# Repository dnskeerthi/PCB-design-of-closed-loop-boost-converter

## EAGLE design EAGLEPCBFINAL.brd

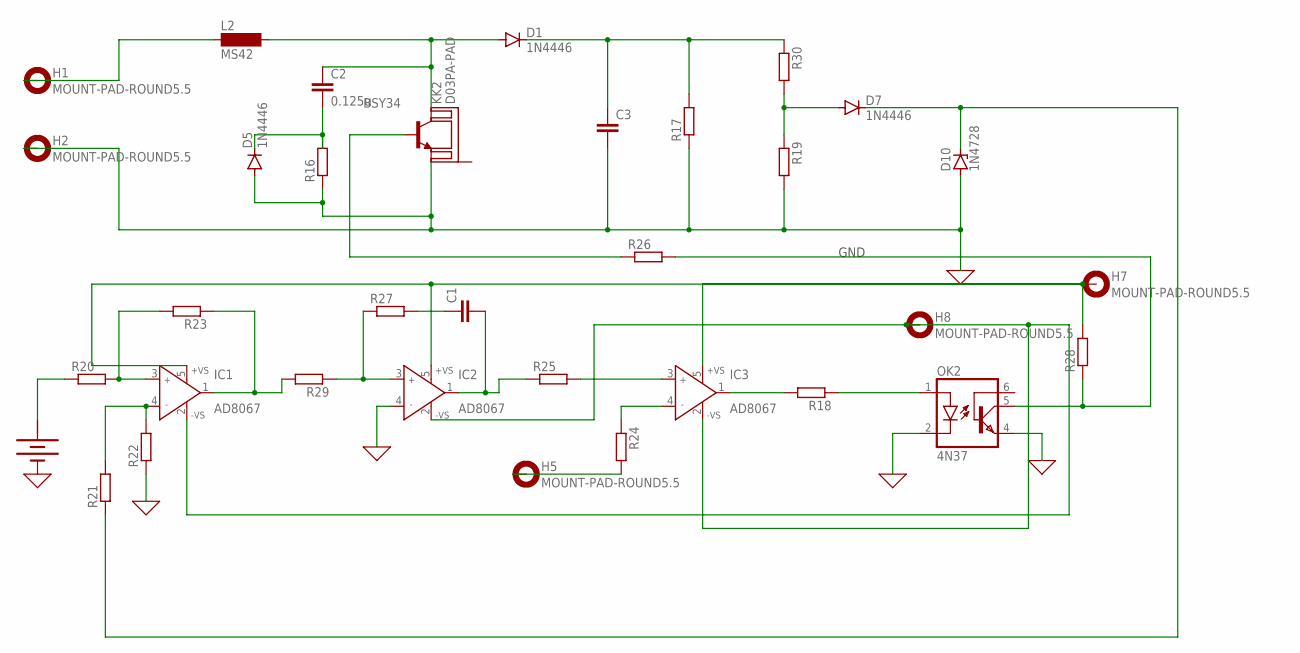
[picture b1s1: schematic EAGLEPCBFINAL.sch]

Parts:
BAT1: BATTERY
C1: C2.5/2; C2.5-2
C2: 0.125u; C5B3.5
C3: C7.5/3; C7.5B3
D1, D5, D7: 1N4446; DO35-10
D10: 1N4728; DO41Z10
H1, H2, H5, H7, H8: MOUNT-PAD-ROUND5.5; 5,5-PAD
IC1, IC2, IC3: AD8067; SOT23-5
KK2: D03PA-PAD
L2: MS42
OK2: 4N37; DIL06
R16, R17: R-EU_0204/2V; 0204V
R18: R-EU_0204/5; 0204/5
R19, R20, R21, R22, R23, R24, R25, R26: R-EU_0207/10; 0207/10
R27: R-EU_0309/12; 0309/12
R28, R29: R-EU_0411/15; 0411/15
R30: R-EU_0922/22; 0922/22
T1: BSY34; TO39

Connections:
0: BAT1.-, C3.2, D5.A, D10.A, H2.B5,5, IC2.4 (IN-), OK2.2 (C), OK2.4 (EMI), R16.1, R17.1, R19.2, R22.1, T1.1 (E)
+: BAT1.+@1 (+)
unnamed: H1.B5,5, L2.1
unnamed: C2.1, D1.A, L2.2, T1.3 (C)
unnamed: C3.1, D1.C, R17.2, R30.1
unnamed: D7.A, R19.1, R30.2
unnamed: C2.2, D5.C, R16.2
unnamed: H8.B5,5, IC1.2 (-VS), IC2.2 (-VS), IC3.2 (-VS)
unnamed: D7.C, D10.C, R21.1
unnamed: BAT1.+, R20.1
unnamed: IC1.3 (IN+), R20.2, R23.2
unnamed: IC1.4 (IN-), R21.2, R22.2
unnamed: IC1.1 (OUT), R23.1, R29.2
unnamed: IC2.3 (IN+), R27.1, R29.1
unnamed: C1.1, R27.2
unnamed: C1.2, IC2.1 (OUT), R25.1
unnamed: IC3.3 (IN+), R25.2
unnamed: IC3.4 (IN-), R24.1
unnamed: IC3.1 (OUT), R18.2
unnamed: OK2.1 (A), R18.1
unnamed: OK2.5 (COL), R26.2, R28.1
unnamed: H7.B5,5, IC1.5 (+VS), IC2.5 (+VS), IC3.5 (+VS), R28.2
unnamed: R26.1, T1.2 (B)
unnamed: H5.B5,5, R24.2

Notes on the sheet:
GND

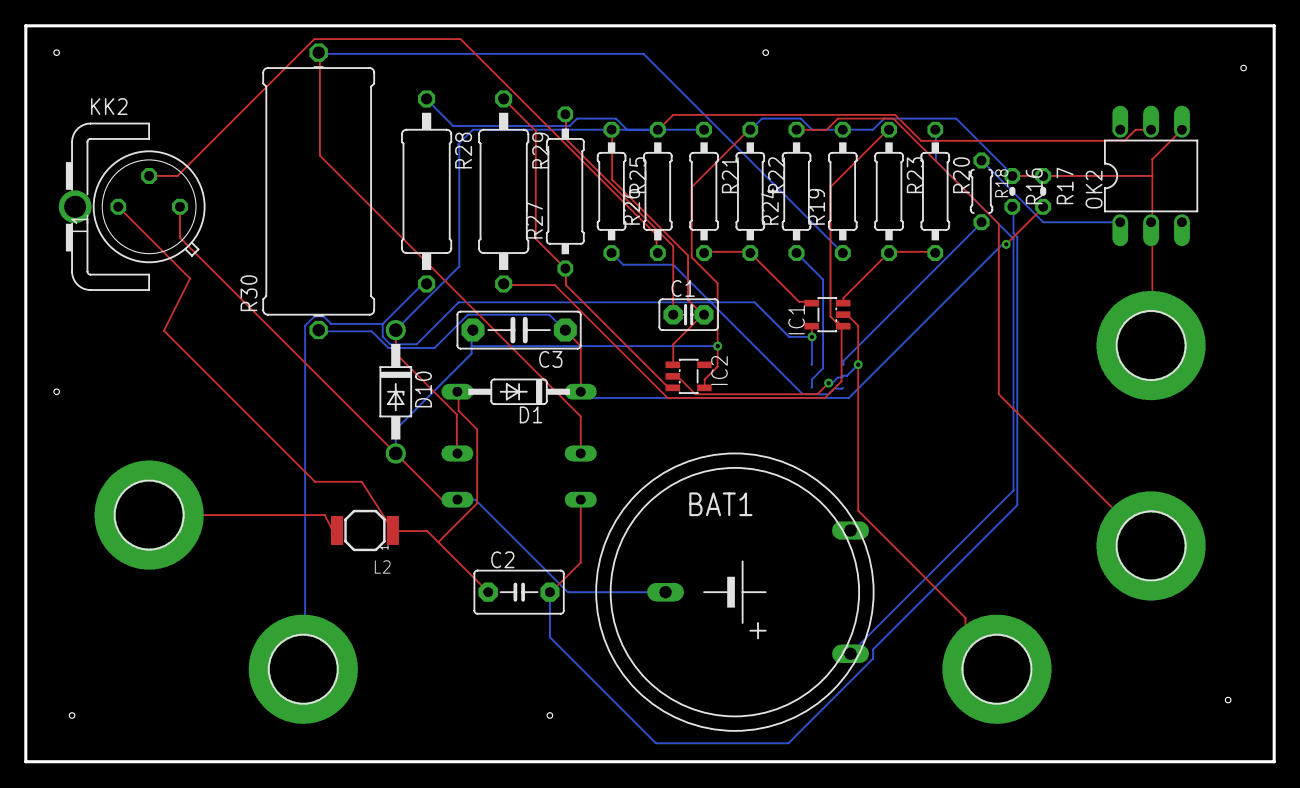
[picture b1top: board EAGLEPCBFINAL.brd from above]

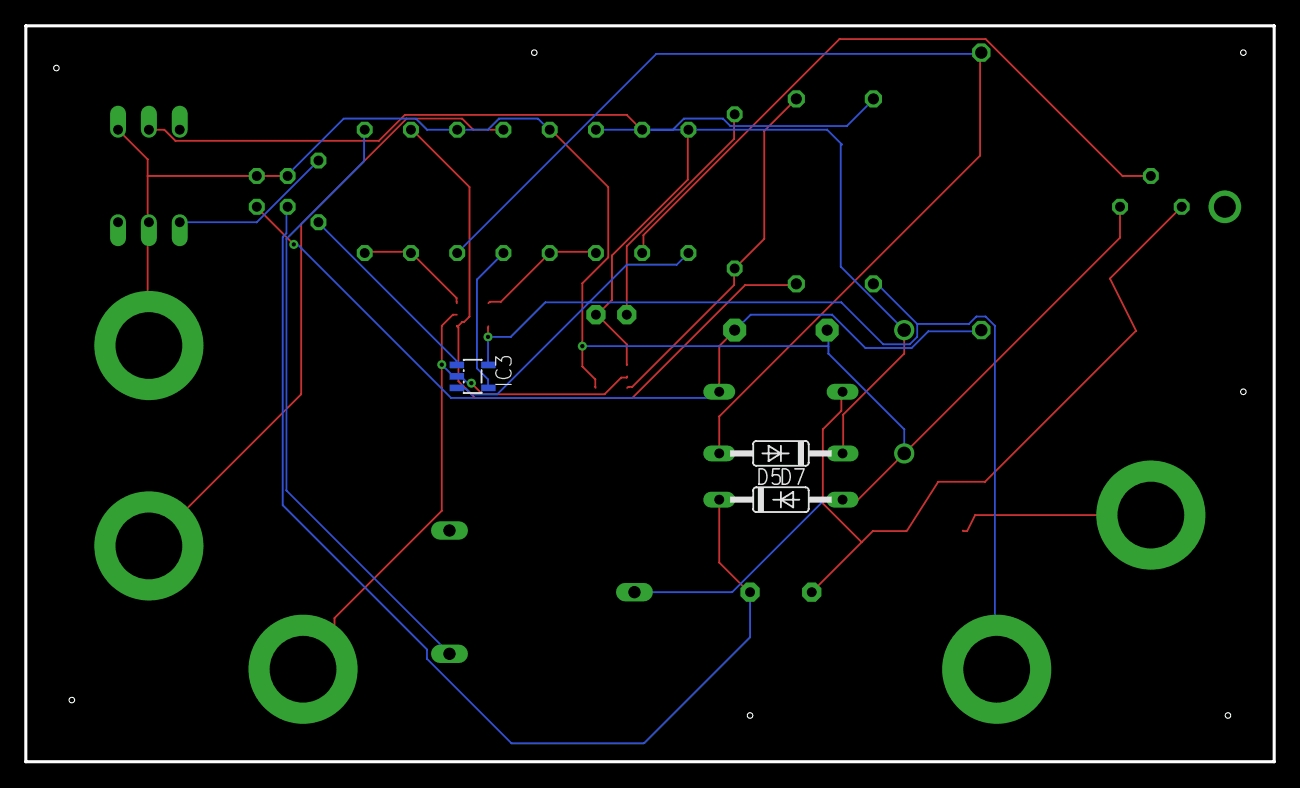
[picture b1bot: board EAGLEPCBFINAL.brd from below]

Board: 2 copper layers, 102.8 x 60.6 mm, 35 parts (3 on the bottom side), 23 nets.
